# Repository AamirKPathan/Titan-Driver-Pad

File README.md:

# FRC 5719 Titan Driver Pad

A custom PCB-based button controller project for FRC 5719. The controller uses a Seeed Studio XIAO ESP32-C3, eight Cherry MX-style mechanical switches, and a small OLED display.

**Enclosure:** Bottom case only. There is no top case or cover.

## Project Images

| Final product | PCB render |
|---|---|
|  |  |

<details>
<summary>Design and development views</summary>

### Schematic

### PCB outline

### Firmware project

### Electrical rules check

</details>

## Project Status

- [x] Firmware builds successfully with PlatformIO.
- [x] OLED and graphics libraries installed.
- [ ] Assemble and test physical hardware.
- [ ] Verify all eight switches and OLED.
- [ ] Develop the PC-side virtual gamepad bridge.
- [ ] Test compatibility with the intended FRC Driver Station setup.

## Hardware

| Component | Details |
|---|---|
| Microcontroller | Seeed Studio XIAO ESP32-C3 |
| Switches | 8 Cherry MX-style mechanical switches |
| Display | 0.91-inch SSD1306 OLED, 128 × 32, I2C |
| PCB design software | KiCad |
| Firmware environment | VS Code + PlatformIO |
| Enclosure | Bottom case only; no top case |

## Controls

| Switch | Intended Input |
|---|---|
| SW1 | Left stick up (W / 1) |
| SW2 | Left stick left (A / 2) |
| SW3 | Left stick down (S / 3) |
| SW4 | Left stick right (D / 4) |
| SW5 | L2 |
| SW6 | R2 |
| SW7 | R1 |
| SW8 | L1 |

Controls are intended to remain active while a switch is held and deactivate when released. Opposite directions cancel each other out.

## Pin Assignments

### Switch Matrix

| Signal | XIAO Pin Label | GPIO |
|---|---|---|
| Row 1 | D0 / A0 | 2 |
| Row 2 | D1 / A1 | 3 |
| Row 3 | D2 / A2 | 4 |
| Row 4 | D3 / A3 | 5 |
| Column 1 | D6 / TX | 8 |
| Column 2 | D7 / RX | 9 |

### Matrix Layout

|  | Column 1 (GPIO 8) | Column 2 (GPIO 9) |
|---|---|---|
| Row 1 (GPIO 2) | SW1 | SW5 |
| Row 2 (GPIO 3) | SW2 | SW6 |
| Row 3 (GPIO 4) | SW3 | SW7 |
| Row 4 (GPIO 5) | SW4 | SW8 |

**Note:** The physical matrix wiring and diode orientation have not yet been verified. Confirm them against the final KiCad schematic and PCB when the hardware arrives.

### OLED Display

| OLED Signal | XIAO Pin Label | GPIO |
|---|---|---|
| SDA | D4 / A4 / SDA | 6 |
| SCL | D5 / A5 / SCL | 7 |

The firmware currently uses I2C address `0x3C`. Some OLED modules use `0x3D`.

## Firmware

The firmware is developed using VS Code and PlatformIO with the Arduino framework for ESP32-C3.

### Build Firmware

Open a terminal in the `Firmware` directory and run:

```bash
pio run
```

### Upload Firmware

Once the hardware arrives, connect the XIAO ESP32-C3 through USB and run:

```bash
pio run --target upload
```

### Open Serial Monitor

```bash
pio device monitor
```

The firmware is intended to output controller states in the following format:

```text
STATE,UP,LEFT,DOWN,RIGHT,L1,L2,R1,R2
```

Each state is represented by `0` (inactive) or `1` (active).

## Software Dependencies

- VS Code
- PlatformIO
- Arduino framework for ESP32-C3
- Adafruit GFX Library
- Adafruit SSD1306 Library

## Current Limitations

- Firmware compilation has succeeded, but the firmware has not yet been tested on physical hardware.
- Switch scanning, debounce behavior, diode orientation, and matrix wiring still require verification.
- OLED operation must be confirmed on the assembled PCB.
- The PC-side virtual gamepad bridge is still to be developed and tested.
- Compatibility with the intended FRC Driver Station setup has not yet been confirmed.

## Hardware Testing Checklist

Once the hardware arrives:

- [ ] Inspect the PCB and verify component orientation.
- [ ] Check power, ground, and possible shorts before connecting USB.
- [ ] Upload the firmware.
- [ ] Confirm that the OLED initializes.
- [ ] Test each switch individually.
- [ ] Verify that every switch activates the correct control.
- [ ] Confirm opposite directions cancel each other.
- [ ] Confirm controls deactivate when switches are released.
- [ ] Test the PC-side virtual gamepad bridge.
- [ ] Verify the intended FRC Driver Station workflow.

## Project Structure

The project may be organized as follows:

```text
Titan Driver Pad/
├── Firmware/
│   ├── platformio.ini
│   └── src/
│       └── main.cpp
├── Hardware/
│   └── KiCad project files
└── README.md
```

Adjust the folder names in this section to match the actual project structure.

## Credits

Developed for FRC Team 5719 — Pink Titans.

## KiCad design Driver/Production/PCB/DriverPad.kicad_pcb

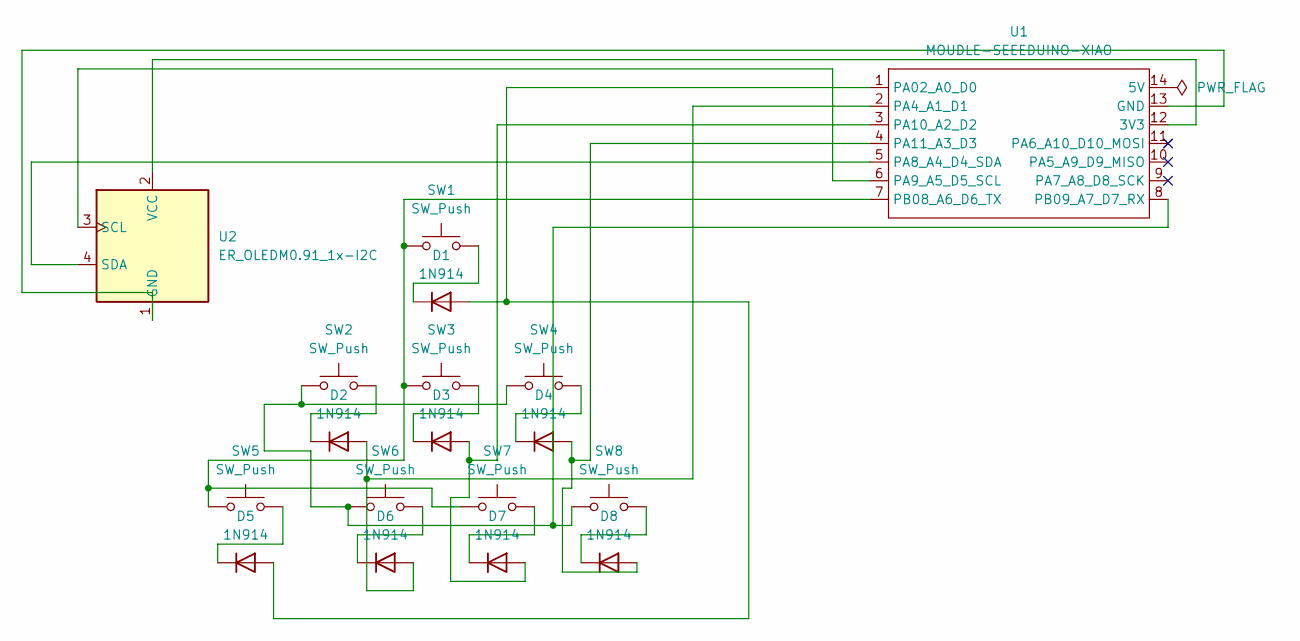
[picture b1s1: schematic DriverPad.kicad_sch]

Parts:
D1, D2, D3, D4, D5, D6, D7, D8: 1N914; D_DO-35_SOD27_P7.62mm_Horizontal
SW1, SW2, SW3, SW4, SW5, SW6, SW7, SW8: SW_Push; SW_Cherry_MX_1.00u_PCB
U1: MOUDLE-SEEEDUINO-XIAO; MCU_Seeed_ESP32C3
U2: ER_OLEDM0.91_1x-I2C

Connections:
unnamed: D1.2 (A), D5.2 (A), U1.1 (PA02_A0_D0)
unnamed: D1.1 (K), SW1.2
unnamed: D2.2 (A), D6.2 (A), U1.2 (PA4_A1_D1)
unnamed: D2.1 (K), SW2.2
unnamed: D3.2 (A), D7.2 (A), U1.3 (PA10_A2_D2)
unnamed: D3.1 (K), SW3.2
unnamed: D4.2 (A), D8.2 (A), U1.4 (PA11_A3_D3)
unnamed: D4.1 (K), SW4.2
unnamed: D5.1 (K), SW5.2
unnamed: D6.1 (K), SW6.2
unnamed: D7.1 (K), SW7.2
unnamed: D8.1 (K), SW8.2
unnamed: U1.12 (3V3), U2.2 (VCC)
unnamed: U1.13 (GND), U2.1 (GND)
unnamed: U1.5 (PA8_A4_D4_SDA), U2.4 (SDA)
unnamed: U1.6 (PA9_A5_D5_SCL), U2.3 (SCL)
unnamed: SW1.1, SW3.1, SW5.1, SW7.1, U1.7 (PB08_A6_D6_TX)
unnamed: SW2.1, SW4.1, SW6.1, SW8.1, U1.8 (PB09_A7_D7_RX)

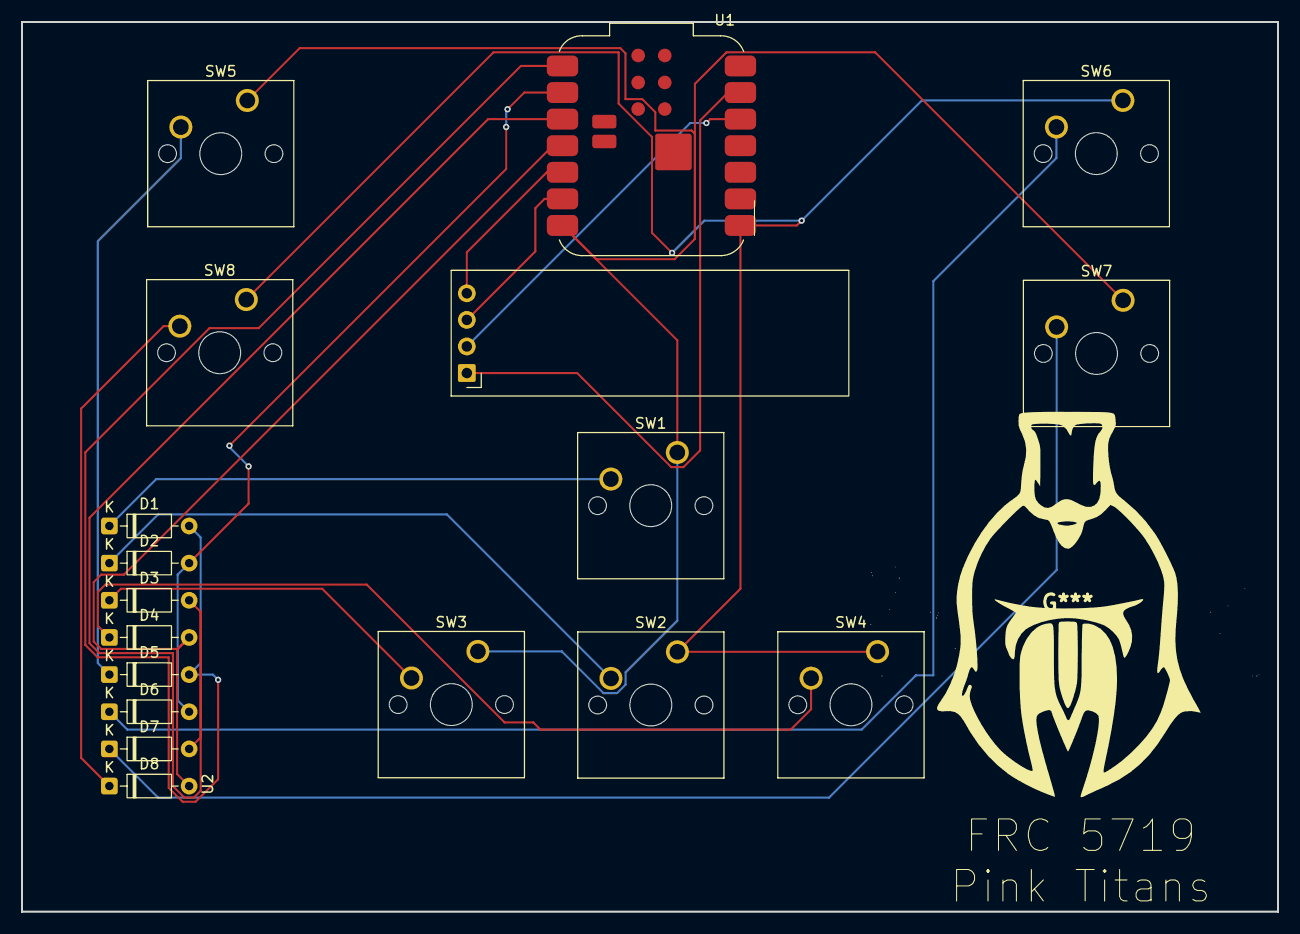
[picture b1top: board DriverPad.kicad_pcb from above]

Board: 2 copper layers, 120.0 x 85.0 mm, 18 parts (0 on the bottom side), 18 nets.
